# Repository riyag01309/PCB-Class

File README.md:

I'm not sure the Edgerton Center logo is correct.

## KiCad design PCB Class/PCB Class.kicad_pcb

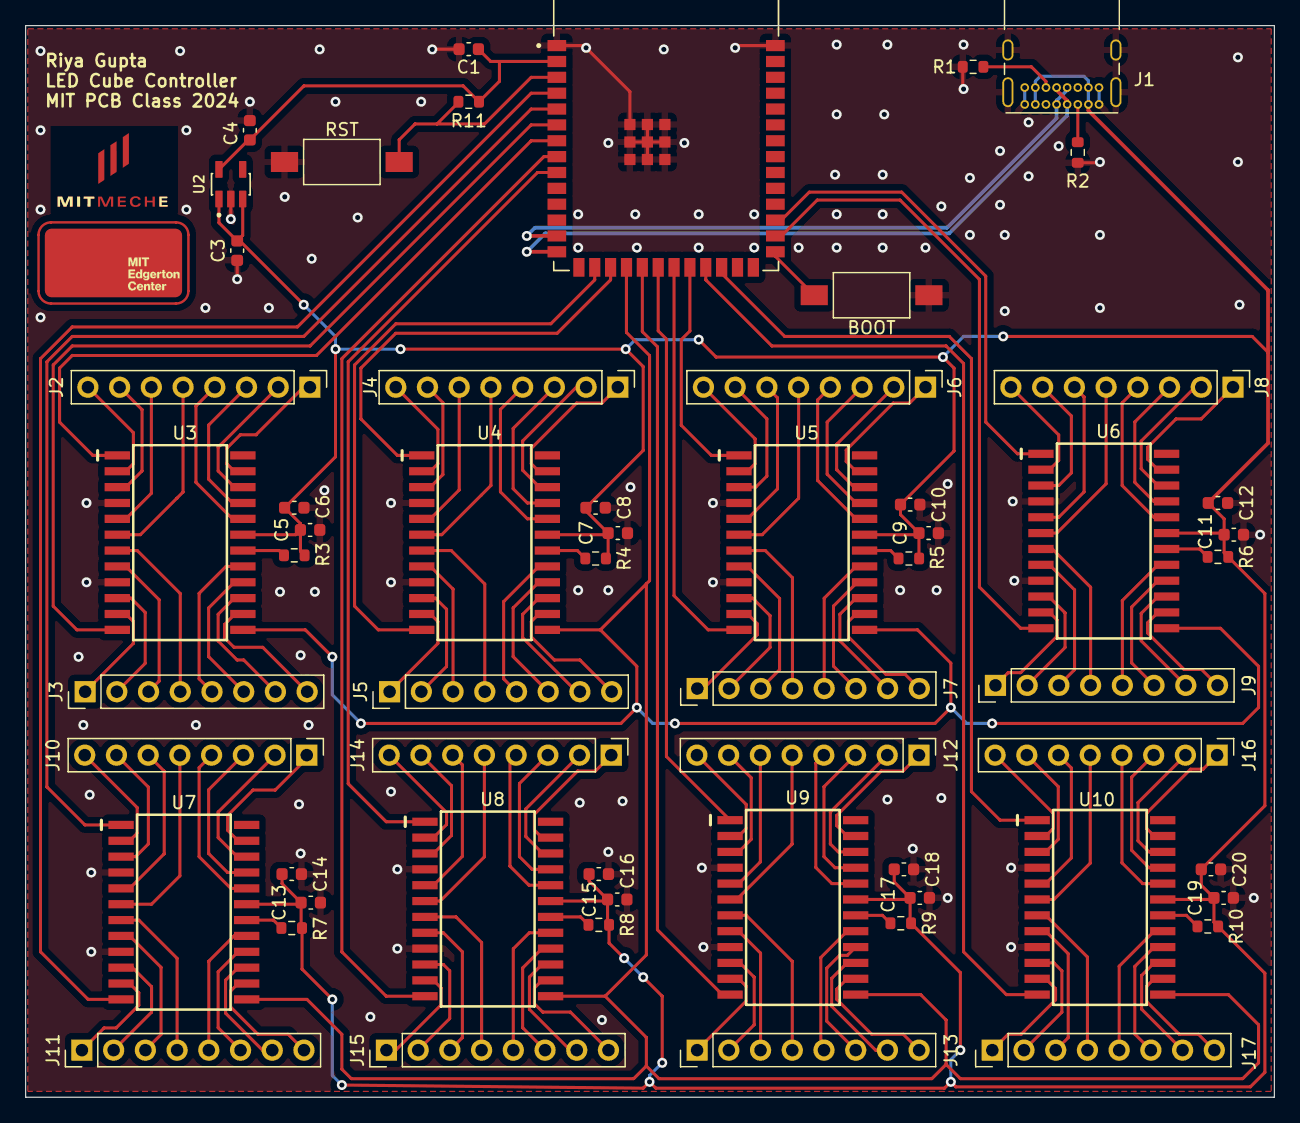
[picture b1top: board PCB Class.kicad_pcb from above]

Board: 2 copper layers, 100.0 x 85.8 mm, 59 parts (0 on the bottom side), 162 nets.

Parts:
BOOT: SW_Push; SW_SPST_FSMSM
C1: 1uF; C_0603_1608Metric
C3, C4: 22uF; C_0603_1608Metric
C5, C7, C9, C11, C13, C15, C17, C19: 0.1uF; C_0603_1608Metric
C6, C8, C10, C12, C14, C16, C18, C20: 10uF; C_0603_1608Metric
J1: USB_C_Receptacle_USB2.0; USB_C_Receptacle_GCT_USB4085
J2, J3, J4, J5, J6, J7, J8, J9, J10, J11, J12, J13, J14, J15, J16, J17: Conn_01x08_Female; PinHeader_1x08_P2.54mm_Vertical
R1, R2: 5.1K; R_0603_1608Metric
R3, R4, R5, R6, R7, R8, R9, R10: 12k; R_0603_1608Metric
R11: 10K; R_0603_1608Metric
RST: SW_Push; SW_SPST_FSMSM
U1: ESP32-S3-WROOM-1-N4; XCVR_ESP32-S3-WROOM-1-N4
U2: AP2112K-3.3TRG1; SOT95P285X140-5N
U3, U4, U5, U6, U7, U8, U9, U10: MAX7219; SOIC24

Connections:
+3.3V: C1.1, C4.1, R11.1, U1.2 (3V3), U2.5 (VOUT)
+5V: C3.1, C5.1, C6.1, C7.1, C8.1, C9.1, C10.1, C11.1, C12.1, C13.1, C14.1, C15.1, C16.1, C17.1, C18.1, C19.1, C20.1, J1.A4 (VBUS), J1.A9 (VBUS), J1.B4 (VBUS), J1.B9 (VBUS), R3.1, R4.1, R5.1, R6.1, R7.1, R8.1, R9.1, R10.1, U2.1 (VIN), U2.3 (EN), U3.19 (V+), U4.19 (V+), U5.19 (V+), U6.19 (V+), U7.19 (V+), U8.19 (V+), U9.19 (V+), U10.19 (V+)
/ESP32/CLK: U1.18 (IO10), U3.13 (CLK), U4.13 (CLK), U5.13 (CLK), U6.13 (CLK), U7.13 (CLK), U8.13 (CLK), U9.13 (CLK), U10.13 (CLK)
/ESP32/D+: J1.A6 (D+), J1.B6 (D+), U1.14 (IO20)
/ESP32/D-: J1.A7 (D-), J1.B7 (D-), U1.13 (IO19)
/ESP32/DIN1: U1.7 (IO7), U3.1 (DIN)
/ESP32/DIN2: U1.17 (IO9), U4.1 (DIN)
/ESP32/DIN3: U1.22 (IO14), U5.1 (DIN)
/ESP32/DIN4: U1.29 (IO36), U6.1 (DIN)
/ESP32/DIN5: U1.5 (IO5), U7.1 (DIN)
/ESP32/DIN6: U1.9 (IO16), U8.1 (DIN)
/ESP32/DIN7: U1.20 (IO12), U9.1 (DIN)
/ESP32/DIN8: U1.24 (IO47), U10.1 (DIN)
/ESP32/LOAD1: U1.6 (IO6), U3.12 (LOAD)
/ESP32/LOAD2: U1.16 (IO46), U4.12 (LOAD)
/ESP32/LOAD3: U1.21 (IO13), U5.12 (LOAD)
/ESP32/LOAD4: U1.28 (IO35), U6.12 (LOAD)
/ESP32/LOAD5: U1.4 (IO4), U7.12 (LOAD)
/ESP32/LOAD6: U1.8 (IO15), U8.12 (LOAD)
/ESP32/LOAD7: U1.19 (IO11), U9.12 (LOAD)
/ESP32/LOAD8: U1.23 (IO21), U10.12 (LOAD)
/ESP32/RST: R11.2, RST.2, U1.3 (EN)
/LED Driver2/C51: J11.8, U7.14 (SEG_A)
/LED Driver2/C52: J11.7, U7.15 (SEG_F)
/LED Driver2/C53: J11.6, U7.16 (SEG_B)
/LED Driver2/C54: J11.5, U7.17 (SEG_G)
/LED Driver2/C55: J10.4, U7.20 (SEG_C)
/LED Driver2/C56: J10.3, U7.21 (SEG_E)
/LED Driver2/C57: J10.2, U7.22 (SEG_DP)
/LED Driver2/C58: J10.1, U7.23 (SEG_D)
/LED Driver2/C61: J15.8, U8.14 (SEG_A)
/LED Driver2/C62: J15.7, U8.15 (SEG_F)
/LED Driver2/C63: J15.6, U8.16 (SEG_B)
/LED Driver2/C64: J15.5, U8.17 (SEG_G)
/LED Driver2/C65: J14.4, U8.20 (SEG_C)
/LED Driver2/C66: J14.3, U8.21 (SEG_E)
/LED Driver2/C67: J14.2, U8.22 (SEG_DP)
/LED Driver2/C68: J14.1, U8.23 (SEG_D)
/LED Driver2/C71: J13.8, U9.14 (SEG_A)
/LED Driver2/C72: J13.7, U9.15 (SEG_F)
/LED Driver2/C73: J13.6, U9.16 (SEG_B)
/LED Driver2/C74: J13.5, U9.17 (SEG_G)
/LED Driver2/C75: J12.4, U9.20 (SEG_C)
/LED Driver2/C76: J12.3, U9.21 (SEG_E)
/LED Driver2/C77: J12.2, U9.22 (SEG_DP)
/LED Driver2/C78: J12.1, U9.23 (SEG_D)
/LED Driver2/C81: J17.8, U10.14 (SEG_A)
/LED Driver2/C82: J17.7, U10.15 (SEG_F)
/LED Driver2/C83: J17.6, U10.16 (SEG_B)
/LED Driver2/C84: J17.5, U10.17 (SEG_G)
/LED Driver2/C85: J16.4, U10.20 (SEG_C)
/LED Driver2/C86: J16.3, U10.21 (SEG_E)
/LED Driver2/C87: J16.2, U10.22 (SEG_DP)
/LED Driver2/C88: J16.1, U10.23 (SEG_D)
/LED Driver2/R51: J10.8, U7.2 (DIG_0)
/LED Driver2/R52: J10.7, U7.3 (DIG_4)
/LED Driver2/R53: J10.6, U7.5 (DIG_6)
/LED Driver2/R54: J10.5, U7.6 (DIG_2)
/LED Driver2/R55: J11.4, U7.7 (DIG_3)
/LED Driver2/R56: J11.3, U7.8 (DIG_7)
/LED Driver2/R57: J11.2, U7.10 (DIG_5)
/LED Driver2/R58: J11.1, U7.11 (DIG_1)
/LED Driver2/R61: J14.8, U8.2 (DIG_0)
/LED Driver2/R62: J14.7, U8.3 (DIG_4)
/LED Driver2/R63: J14.6, U8.5 (DIG_6)
/LED Driver2/R64: J14.5, U8.6 (DIG_2)
/LED Driver2/R65: J15.4, U8.7 (DIG_3)
/LED Driver2/R66: J15.3, U8.8 (DIG_7)
/LED Driver2/R67: J15.2, U8.10 (DIG_5)
/LED Driver2/R68: J15.1, U8.11 (DIG_1)
/LED Driver2/R71: J12.8, U9.2 (DIG_0)
/LED Driver2/R72: J12.7, U9.3 (DIG_4)
/LED Driver2/R73: J12.6, U9.5 (DIG_6)
/LED Driver2/R74: J12.5, U9.6 (DIG_2)
/LED Driver2/R75: J13.4, U9.7 (DIG_3)
/LED Driver2/R76: J13.3, U9.8 (DIG_7)
/LED Driver2/R77: J13.2, U9.10 (DIG_5)
/LED Driver2/R78: J13.1, U9.11 (DIG_1)
/LED Driver2/R81: J16.8, U10.2 (DIG_0)
/LED Driver2/R82: J16.7, U10.3 (DIG_4)
/LED Driver2/R83: J16.6, U10.5 (DIG_6)
/LED Driver2/R84: J16.5, U10.6 (DIG_2)
/LED Driver2/R85: J17.4, U10.7 (DIG_3)
/LED Driver2/R86: J17.3, U10.8 (DIG_7)
/LED Driver2/R87: J17.2, U10.10 (DIG_5)
/LED Driver2/R88: J17.1, U10.11 (DIG_1)
/LED Driver/C11: J3.8, U3.14 (SEG_A)
/LED Driver/C12: J3.7, U3.15 (SEG_F)
/LED Driver/C13: J3.6, U3.16 (SEG_B)
/LED Driver/C14: J3.5, U3.17 (SEG_G)
/LED Driver/C15: J2.4, U3.20 (SEG_C)
/LED Driver/C16: J2.3, U3.21 (SEG_E)
/LED Driver/C17: J2.2, U3.22 (SEG_DP)
/LED Driver/C18: J2.1, U3.23 (SEG_D)
/LED Driver/C21: J5.8, U4.14 (SEG_A)
/LED Driver/C22: J5.7, U4.15 (SEG_F)
/LED Driver/C23: J5.6, U4.16 (SEG_B)
/LED Driver/C24: J5.5, U4.17 (SEG_G)
/LED Driver/C25: J4.4, U4.20 (SEG_C)
/LED Driver/C26: J4.3, U4.21 (SEG_E)
/LED Driver/C27: J4.2, U4.22 (SEG_DP)
/LED Driver/C28: J4.1, U4.23 (SEG_D)
/LED Driver/C31: J7.8, U5.14 (SEG_A)
/LED Driver/C32: J7.7, U5.15 (SEG_F)
/LED Driver/C33: J7.6, U5.16 (SEG_B)
/LED Driver/C34: J7.5, U5.17 (SEG_G)
/LED Driver/C35: J6.4, U5.20 (SEG_C)
/LED Driver/C36: J6.3, U5.21 (SEG_E)
/LED Driver/C37: J6.2, U5.22 (SEG_DP)
/LED Driver/C38: J6.1, U5.23 (SEG_D)
/LED Driver/C41: J9.8, U6.14 (SEG_A)
/LED Driver/C42: J9.7, U6.15 (SEG_F)
/LED Driver/C43: J9.6, U6.16 (SEG_B)
/LED Driver/C44: J9.5, U6.17 (SEG_G)
/LED Driver/C45: J8.4, U6.20 (SEG_C)
/LED Driver/C46: J8.3, U6.21 (SEG_E)
/LED Driver/C47: J8.2, U6.22 (SEG_DP)
/LED Driver/C48: J8.1, U6.23 (SEG_D)
/LED Driver/R11: J2.8, U3.2 (DIG_0)
/LED Driver/R12: J2.7, U3.3 (DIG_4)
/LED Driver/R13: J2.6, U3.5 (DIG_6)
/LED Driver/R14: J2.5, U3.6 (DIG_2)
/LED Driver/R15: J3.4, U3.7 (DIG_3)
/LED Driver/R16: J3.3, U3.8 (DIG_7)
/LED Driver/R17: J3.2, U3.10 (DIG_5)
/LED Driver/R18: J3.1, U3.11 (DIG_1)
/LED Driver/R21: J4.8, U4.2 (DIG_0)
/LED Driver/R22: J4.7, U4.3 (DIG_4)
/LED Driver/R23: J4.6, U4.5 (DIG_6)
/LED Driver/R24: J4.5, U4.6 (DIG_2)
/LED Driver/R25: J5.4, U4.7 (DIG_3)
/LED Driver/R26: J5.3, U4.8 (DIG_7)
/LED Driver/R27: J5.2, U4.10 (DIG_5)
/LED Driver/R28: J5.1, U4.11 (DIG_1)
/LED Driver/R31: J6.8, U5.2 (DIG_0)
/LED Driver/R32: J6.7, U5.3 (DIG_4)
/LED Driver/R33: J6.6, U5.5 (DIG_6)
/LED Driver/R34: J6.5, U5.6 (DIG_2)
/LED Driver/R35: J7.4, U5.7 (DIG_3)
/LED Driver/R36: J7.3, U5.8 (DIG_7)
/LED Driver/R37: J7.2, U5.10 (DIG_5)
/LED Driver/R38: J7.1, U5.11 (DIG_1)
/LED Driver/R41: J8.8, U6.2 (DIG_0)
/LED Driver/R42: J8.7, U6.3 (DIG_4)
/LED Driver/R43: J8.6, U6.5 (DIG_6)
/LED Driver/R44: J8.5, U6.6 (DIG_2)
/LED Driver/R45: J9.4, U6.7 (DIG_3)
/LED Driver/R46: J9.3, U6.8 (DIG_7)
/LED Driver/R47: J9.2, U6.10 (DIG_5)
/LED Driver/R48: J9.1, U6.11 (DIG_1)
/USB_C/CC1: J1.A5 (CC1), R2.1
/USB_C/CC2: J1.B5 (CC2), R1.1
GND: BOOT.1, C1.2, C3.2, C4.2, C5.2, C6.2, C7.2, C8.2, C9.2, C10.2, C11.2, C12.2, C13.2, C14.2, C15.2, C16.2, C17.2, C18.2, C19.2, C20.2, J1.A1 (GND), J1.A12 (GND), J1.B1 (GND), J1.B12 (GND), J1.S1 (SHIELD), R1.2, R2.2, RST.1, U1.1 (GND), U1.40 (GND__1), U1.41_1 (GND__2), U1.41_2 (GND__3), U1.41_3 (GND__4), U1.41_4 (GND__5), U1.41_5 (GND__6), U1.41_6 (GND__7), U1.41_7 (GND__8), U1.41_8 (GND__9), U1.41_9 (GND__10), U2.2 (GND), U3.4 (GND), U3.9 (GND), U4.4 (GND), U4.9 (GND), U5.4 (GND), U5.9 (GND), U6.4 (GND), U6.9 (GND), U7.4 (GND), U7.9 (GND), U8.4 (GND), U8.9 (GND), U9.4 (GND), U9.9 (GND), U10.4 (GND), U10.9 (GND)
unnamed: R3.2, U3.18 (ISET)
unnamed: R4.2, U4.18 (ISET)
unnamed: R5.2, U5.18 (ISET)
unnamed: R6.2, U6.18 (ISET)
unnamed: R7.2, U7.18 (ISET)
unnamed: R8.2, U8.18 (ISET)
unnamed: R9.2, U9.18 (ISET)
unnamed: R10.2, U10.18 (ISET)
unnamed: BOOT.2, U1.27 (IO0)

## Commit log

2024-01-11 Schematic Assignment
2024-01-11 Create README.md
    Schematic Submission
2024-01-13 Final Schematic
2024-01-16 Footprints
2024-01-18 Layout
2024-01-18 Layout V2
2024-01-20 Final Layout
